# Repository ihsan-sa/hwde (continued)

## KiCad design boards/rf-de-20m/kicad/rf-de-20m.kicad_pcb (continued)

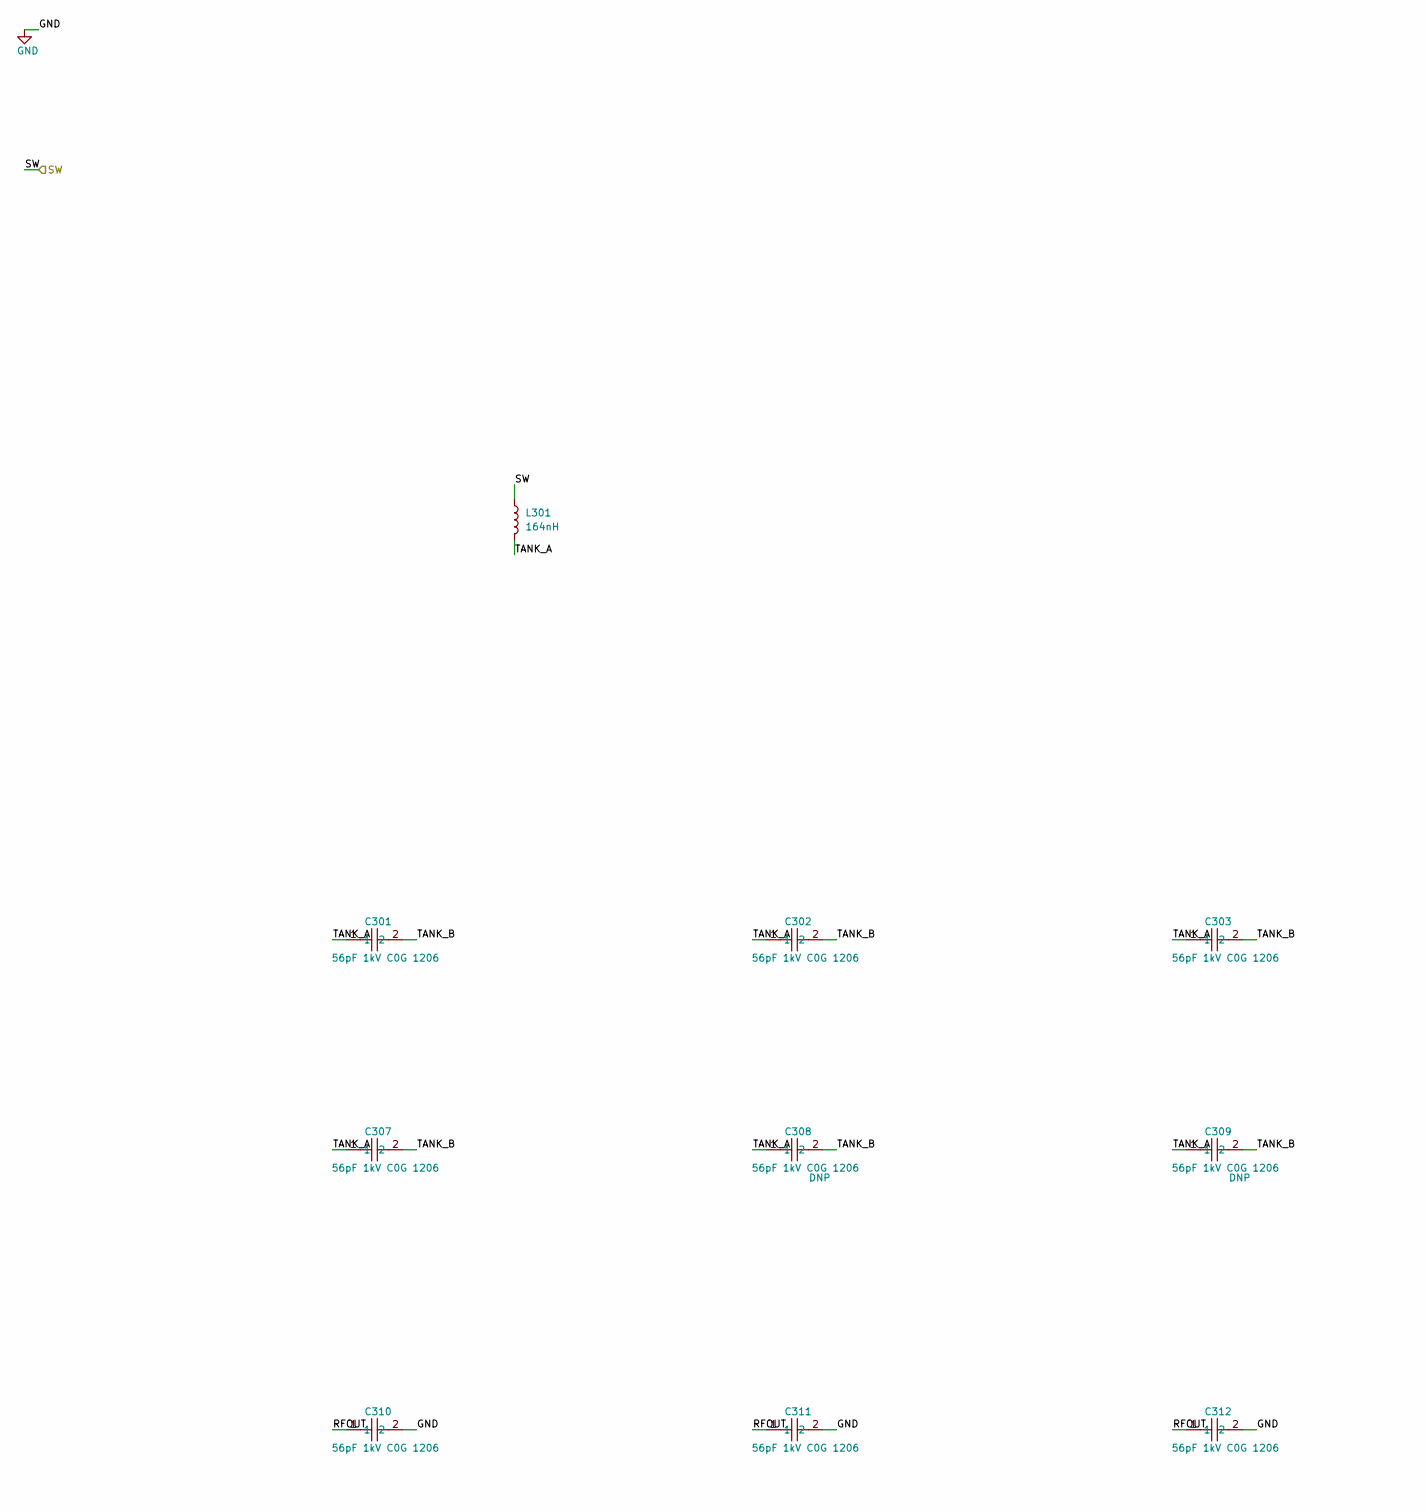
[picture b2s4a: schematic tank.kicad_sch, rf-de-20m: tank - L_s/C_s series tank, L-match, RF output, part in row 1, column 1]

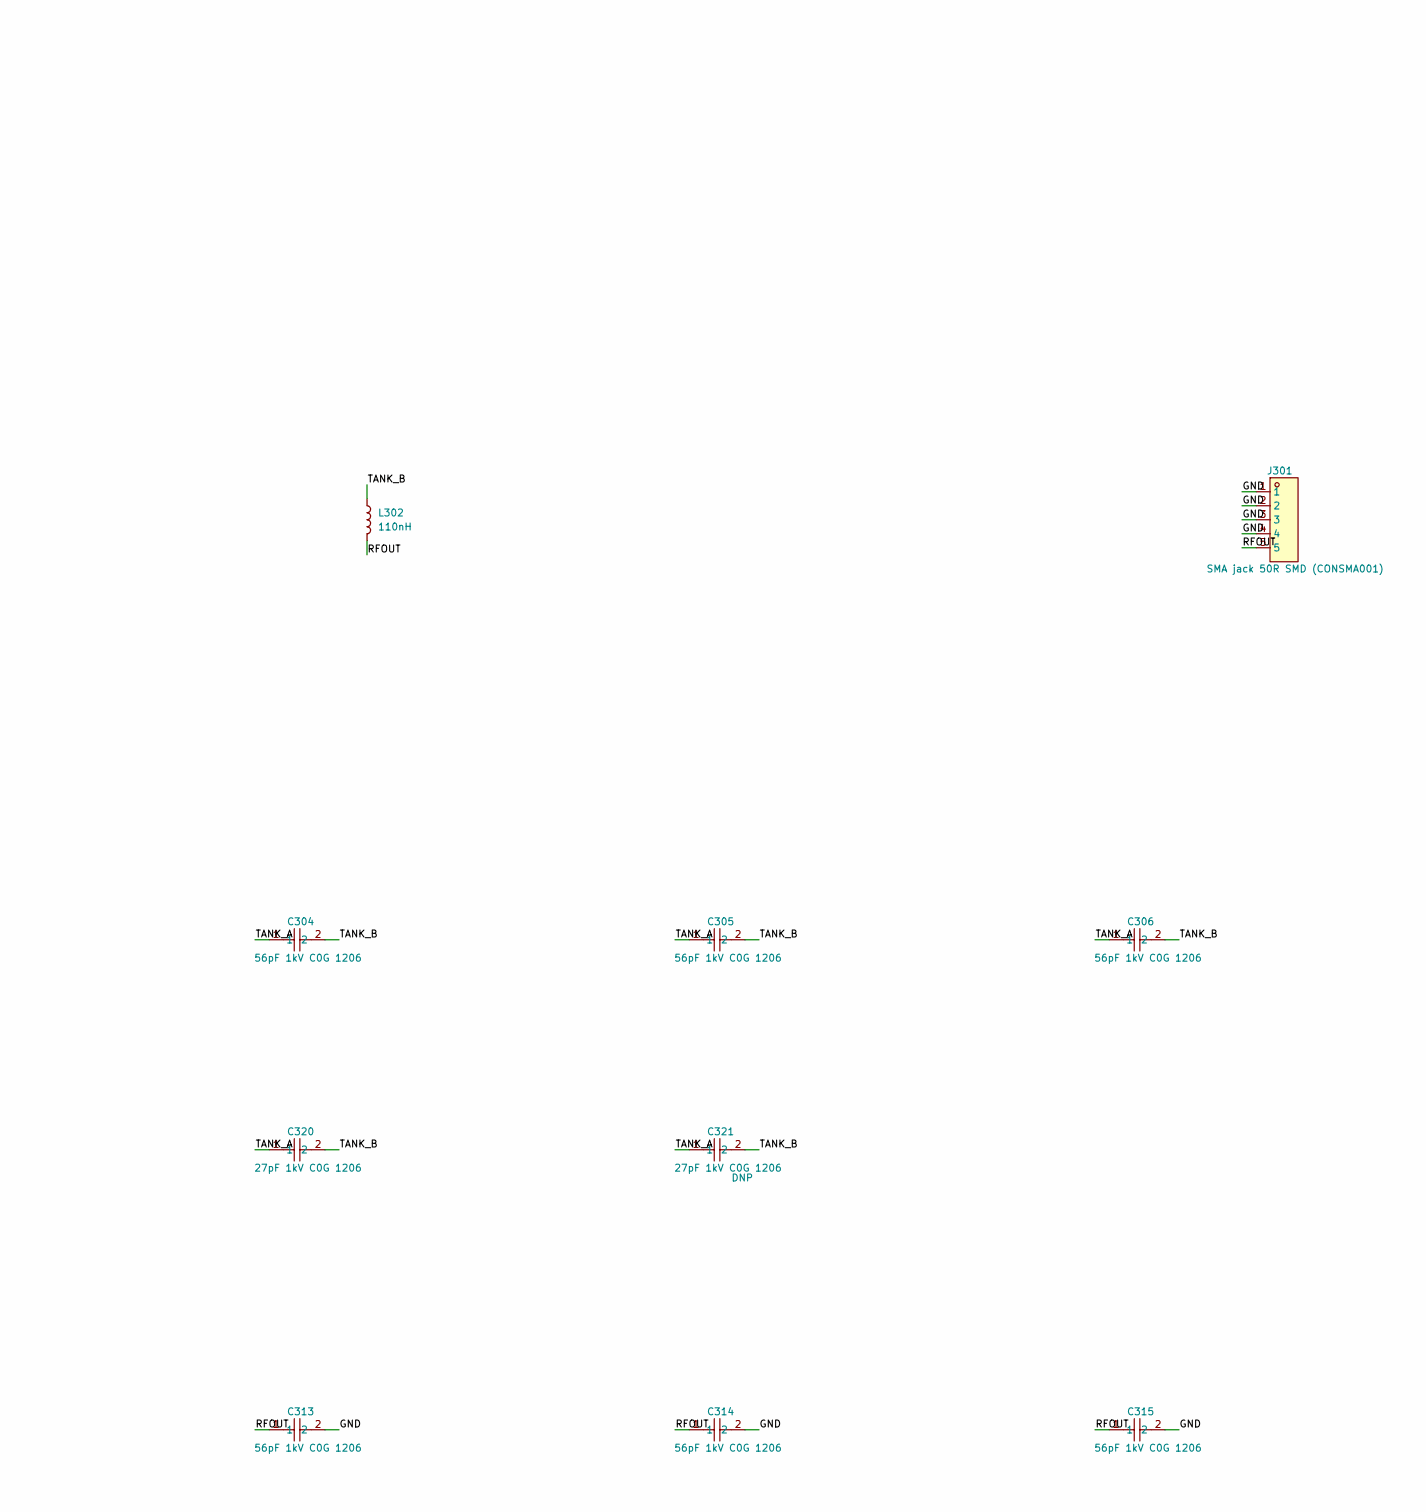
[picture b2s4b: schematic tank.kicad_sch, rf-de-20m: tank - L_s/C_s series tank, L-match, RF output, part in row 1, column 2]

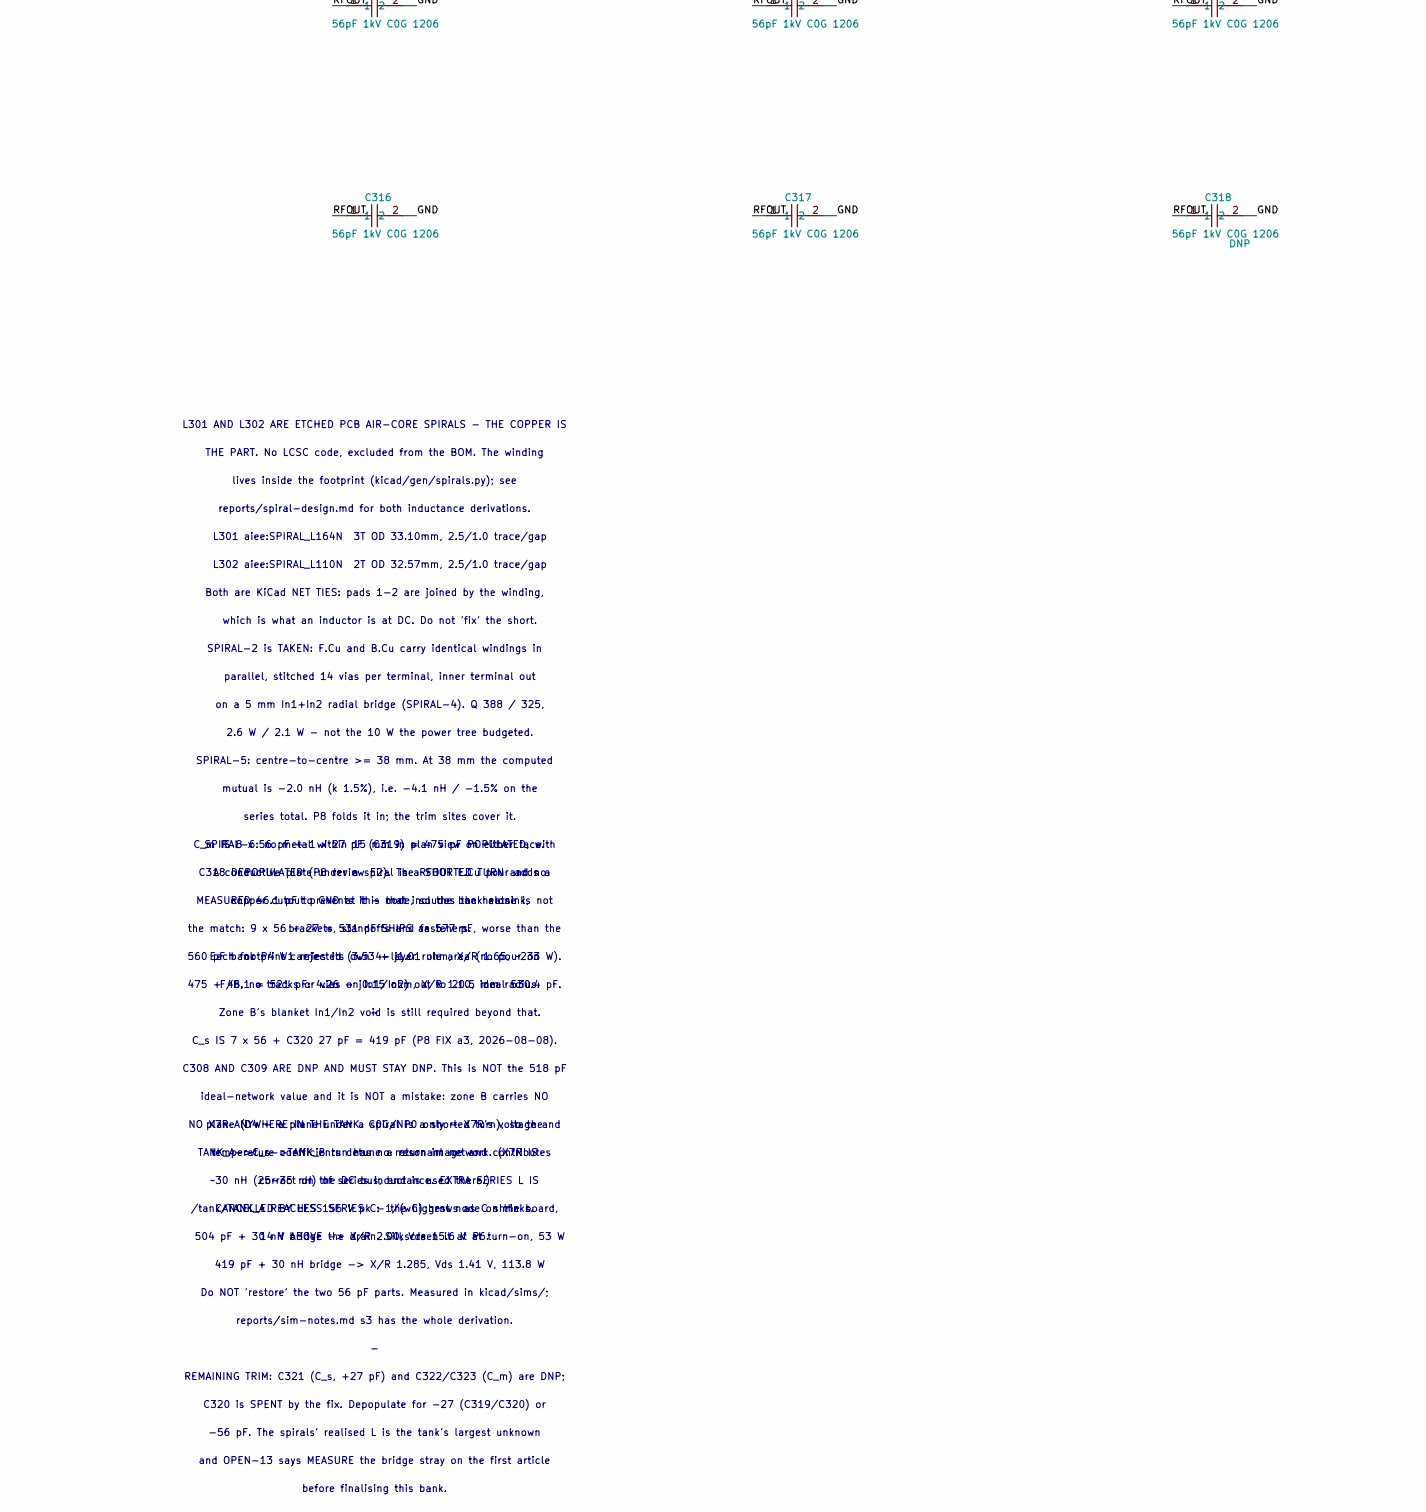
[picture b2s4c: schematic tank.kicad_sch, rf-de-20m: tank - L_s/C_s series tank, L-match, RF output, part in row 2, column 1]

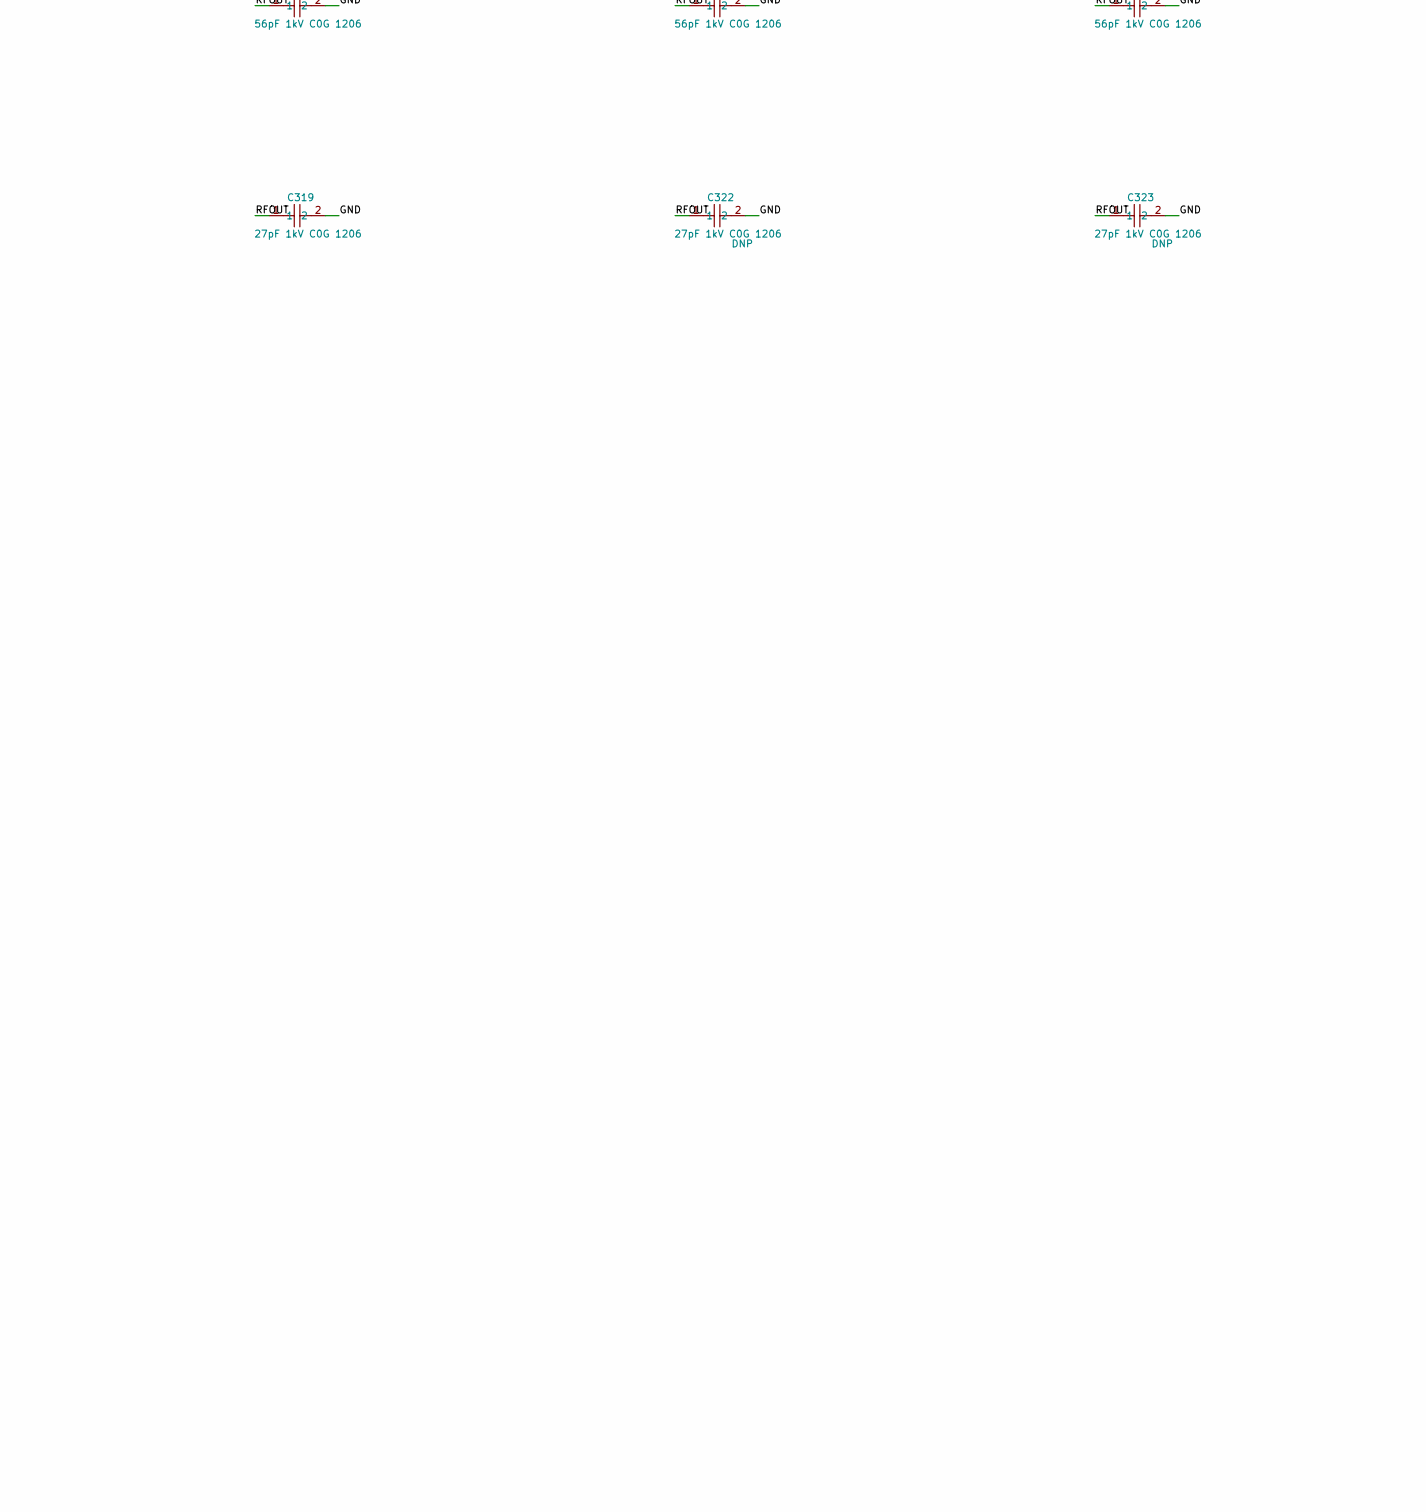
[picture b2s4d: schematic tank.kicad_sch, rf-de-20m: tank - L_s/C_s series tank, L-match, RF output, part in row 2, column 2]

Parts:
C301, C302, C303, C304, C305, C306, C307, C308, C309, C310, C311, C312, C313, C314, C315, C316, C317, C318: 56pF 1kV C0G 1206; C1206; LCSC C113875
C319, C320, C321, C322, C323: 27pF 1kV C0G 1206; C1206; LCSC C541492
J301: SMA jack 50R SMD (CONSMA001); SMA-SMD_CONSMA001-SMD-G-T; LCSC C22418168
L301: 164nH; SPIRAL_L164N
L302: 110nH; SPIRAL_L110N

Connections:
/SW: L301.1; also elsewhere on the board
/tank/RFOUT: C310.1, C311.1, C312.1, C313.1, C314.1, C315.1, C316.1, C317.1, C318.1, C319.1, C322.1, C323.1, J301.5, L302.2
/tank/TANK_A: C301.1, C302.1, C303.1, C304.1, C305.1, C306.1, C307.1, C308.1, C309.1, C320.1, C321.1, L301.2
/tank/TANK_B: C301.2, C302.2, C303.2, C304.2, C305.2, C306.2, C307.2, C308.2, C309.2, C320.2, C321.2, L302.1
GND: C310.2, C311.2, C312.2, C313.2, C314.2, C315.2, C316.2, C317.2, C318.2, C319.2, C322.2, C323.2, J301.1, J301.2, J301.3, J301.4; also elsewhere on the board

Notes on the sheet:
L301 AND L302 ARE ETCHED PCB AIR-CORE SPIRALS - THE COPPER IS
THE PART. No LCSC code, excluded from the BOM. The winding
lives inside the footprint (kicad/gen/spirals.py); see
reports/spiral-design.md for both inductance derivations.
L301 aiee:SPIRAL_L164N 3T OD 33.10mm, 2.5/1.0 trace/gap
L302 aiee:SPIRAL_L110N 2T OD 32.57mm, 2.5/1.0 trace/gap
Both are KiCad NET TIES: pads 1-2 are joined by the winding,
which is what an inductor is at DC. Do not 'fix' the short.
SPIRAL-2 is TAKEN: F.Cu and B.Cu carry identical windings in
parallel, stitched 14 vias per terminal, inner terminal out
on a 5 mm In1+In2 radial bridge (SPIRAL-4). Q 388 / 325,
2.6 W / 2.1 W - not the 10 W the power tree budgeted.
SPIRAL-5: centre-to-centre >= 38 mm. At 38 mm the computed
mutual is -2.0 nH (k 1.5%), i.e. -4.1 nH / -1.5% on the
series total. P8 folds it in; the trim sites cover it.
SPIRAL-6: no metal within 15 mm in plan view on either face.
A conductive plate under a spiral is a SHORTED TURN and no
copper cutout prevents it - that includes the heatsink,
brackets, standoffs and fasteners.
Each footprint carries its own 4-layer rule area (no pour on
F/B, no tracks or vias on In1/In2) out to 20.5 mm radius.
Zone B's blanket In1/In2 void is still required beyond that.
C_m IS 8 x 56 pF + 1 x 27 pF (C319) = 475 pF POPULATED, with
C318 DEPOPULATED (P8 review E2). The RFOUT F.Cu pour adds a
MEASURED 46.1 pF to GND at this node, so the bank alone is not
the match: 9 x 56 + 27 = 531 pF SHIPS as 577 pF, worse than the
560 pF bank P4 W1 rejected (3.53 + j1.01 ohm, X/R 1.65, ~233 W).
475 + 46.1 = 521 pF: 4.26 - j0.15 ohm, X/R 1.10, ideal 530.4 pF.
C_s IS 7 x 56 + C320 27 pF = 419 pF (P8 FIX a3, 2026-08-08).
C308 AND C309 ARE DNP AND MUST STAY DNP. This is NOT the 518 pF
ideal-network value and it is NOT a mistake: zone B carries NO
plane (D4 - a plane under a spiral is a shorted turn), so the
TANK_A->C_s->TANK_B run has no return image and contributes
~30 nH (25-35 nH) of series inductance. EXTRA SERIES L IS
CANCELLED BY LESS SERIES C: 1/(wC) grows as C shrinks.
504 pF + 30 nH bridge -> X/R 2.00, Vds 15.6 V at turn-on, 53 W
419 pF + 30 nH bridge -> X/R 1.285, Vds 1.41 V, 113.8 W
Do NOT 'restore' the two 56 pF parts. Measured in kicad/sims/;
reports/sim-notes.md s3 has the whole derivation.
REMAINING TRIM: C321 (C_s, +27 pF) and C322/C323 (C_m) are DNP;

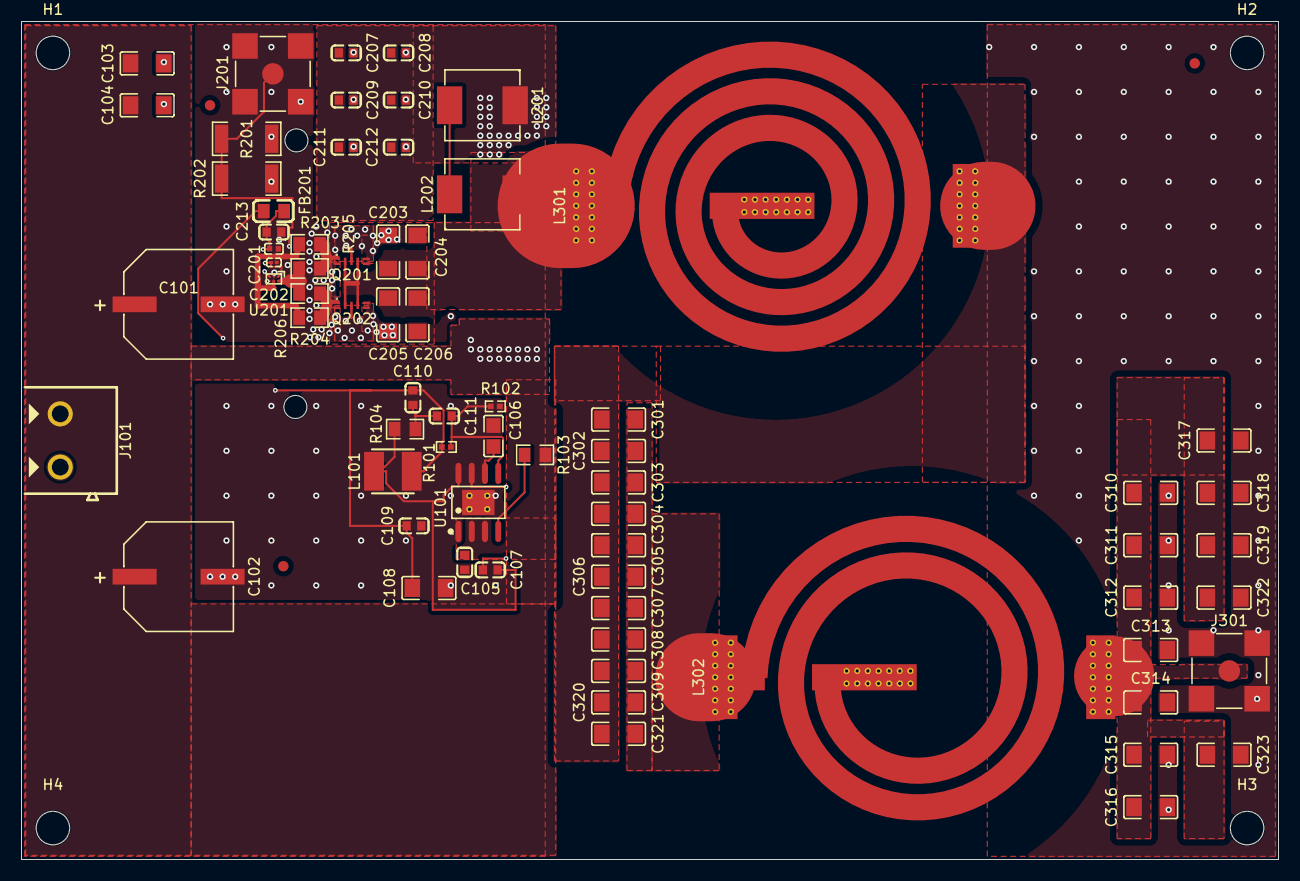
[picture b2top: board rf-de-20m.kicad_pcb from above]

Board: 4 copper layers, 120.0 x 80.0 mm, 80 parts (0 on the bottom side), 20 nets.

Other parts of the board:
FID1, FID2, FID3: Fiducial_1mm_Mask2mm
H1, H2, H3, H4: MountingHole_3.2mm_M3
H5, H6: MountingHole_2.2mm_M2_ISO7380
HS1: HEATSINK_LAND; HS2_HEATSINK_LAND

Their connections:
GND: HS1.1; also elsewhere on the board

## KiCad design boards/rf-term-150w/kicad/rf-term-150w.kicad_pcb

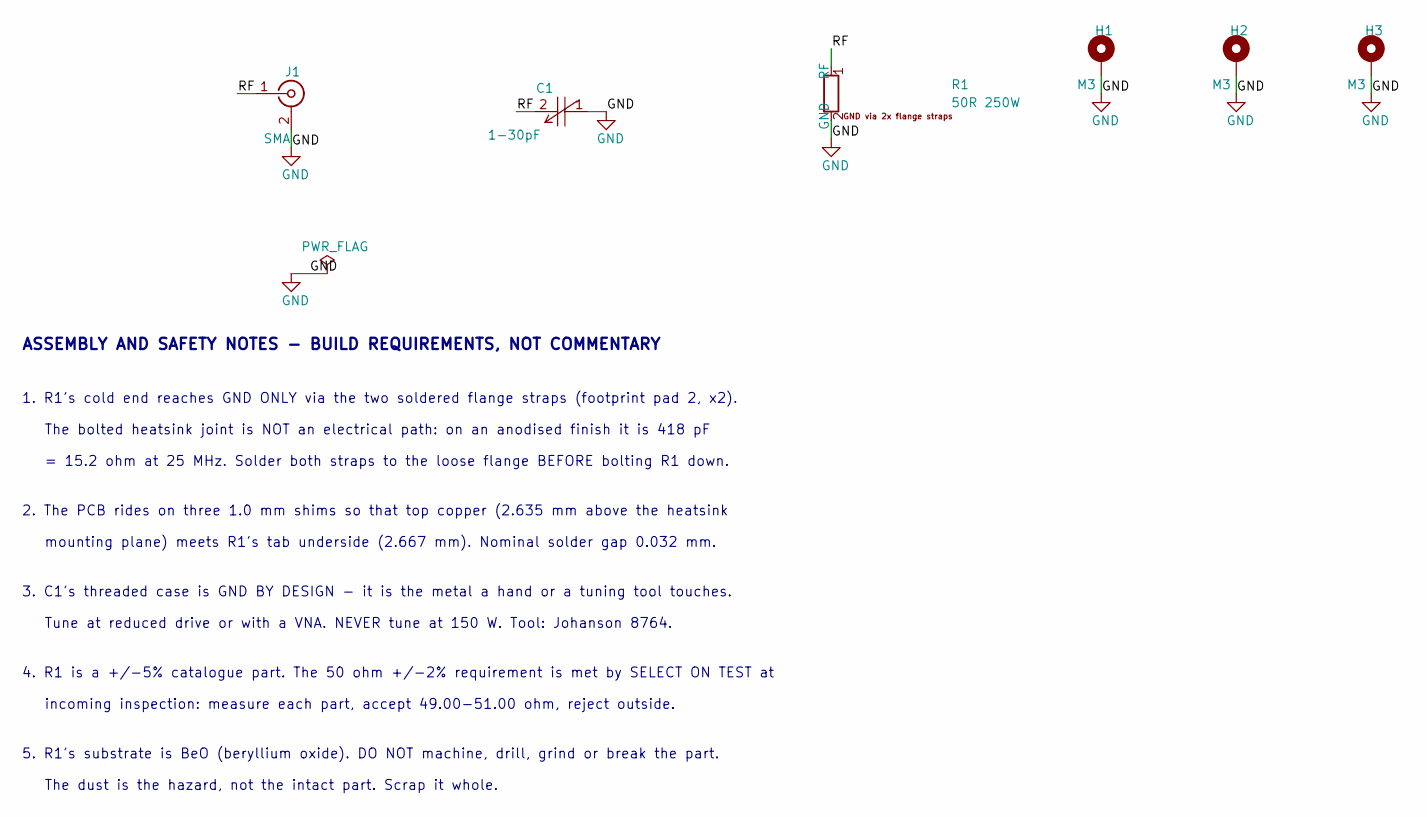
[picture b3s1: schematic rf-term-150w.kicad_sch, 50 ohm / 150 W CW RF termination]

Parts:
C1: 1-30pF; CAP-ADJ-TH_2P-BD7.5_5602; MPN 5602; DigiKey 1956-1000-ND
H1, H2, H3: M3; MountingHole_3.2mm_M3_Pad_5.0mm
J1: SMA; SMA_BAT_Wireless_BWSMA-KWE-Z001; MPN SMA-KWE; LCSC C7498154
R1: 50R 250W; R_LapPad_T50R0-250-12X; MPN T50R0-250-12X; DigiKey 4353-T50R0-250-12X-ND

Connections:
/RF: C1.2 (ROTOR), J1.1 (In), R1.1 (RF)
GND: C1.1 (STATOR), H1.1, H2.1, H3.1, J1.2 (Ext), R1.2 (GND)

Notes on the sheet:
ASSEMBLY AND SAFETY NOTES - BUILD REQUIREMENTS, NOT COMMENTARY
1. R1's cold end reaches GND ONLY via the two soldered flange straps (footprint pad 2, x2).
The bolted heatsink joint is NOT an electrical path: on an anodised finish it is 418 pF
= 15.2 ohm at 25 MHz. Solder both straps to the loose flange BEFORE bolting R1 down.
2. The PCB rides on three 1.0 mm shims so that top copper (2.635 mm above the heatsink
mounting plane) meets R1's tab underside (2.667 mm). Nominal solder gap 0.032 mm.
3. C1's threaded case is GND BY DESIGN - it is the metal a hand or a tuning tool touches.
Tune at reduced drive or with a VNA. NEVER tune at 150 W. Tool: Johanson 8764.
4. R1 is a +/-5% catalogue part. The 50 ohm +/-2% requirement is met by SELECT ON TEST at
incoming inspection: measure each part, accept 49.00-51.00 ohm, reject outside.
5. R1's substrate is BeO (beryllium oxide). DO NOT machine, drill, grind or break the part.
The dust is the hazard, not the intact part. Scrap it whole.

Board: 2 copper layers, 6 parts (0 on the bottom side), 2 nets, no tracks yet.

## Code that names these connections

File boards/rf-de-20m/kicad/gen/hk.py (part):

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TWO OTHER P3 PLACEHOLDERS RESOLVED HERE (parts.json asked P4 to size them)
--------------------------------------------------------------------------
  * **R103 (RON) = 100 k stands, but the PACKAGE moved 0402 -> 0805.**
    (P4 review W2.) RON sits from the RON pin - held near ground by the
    on-timer - to +40V, so the FULL bus stands across one chip resistor
    continuously. A thick-film 0402's maximum WORKING voltage is 50 V, so
    40 V DC is 80 % of it with nothing left for the ~51 V LC turn-on
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  re-VALUEs it to "+40V" - a power symbol's exported net name is its VALUE
  field (LEARNINGS 2026-07-28 [kicad]).
* Six nets are sheet-internal and come out `/hk/<NAME>`: VCC, BST, BUCK_SW,
  FB, RON, RINJ. No constraint references any of them.
* **The buck's switch node is called BUCK_SW, not SW.** `/SW` is the RF drain
  node on `stage`/`tank` and is named in six constraints.json entries; a
  second net called SW anywhere would be a different net with a colliding
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    # L101 - buck inductor, BUCK_SW -> +5V. 22 uH: see docstring.
    _add(sh, "L101", S_L101, V_L101, (152.4, 279.4), footprint=F_L101,
         expect={"1": "1", "2": "2"})
    sh.wire_pins("L101", {"1": BUCK_SW, "2": V5})

    # C107 - BOOTSTRAP, BST to SW. 10 nF per datasheet s8.2.1.2.6 (P3's
    # 2.2 nF was explicitly a placeholder). Must withstand BST-to-SW abs max
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    _add(sh, "C107", S_C10N_100V, V_C10N, (228.6, 279.4), footprint=F_C0603,
         expect={"1": "1", "2": "2"},
         note="Bootstrap BST-SW, 0.01uF per LM5017 s8.2.1.2.6")
    sh.wire_pins("C107", {"1": BST, "2": BUCK_SW})

    # Output bulk + HF on +5V. C108 is the COUT the ripple-injection network
    # exists to compensate for (its ESR is far below the 25 mV COT floor).
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    sh.wire_pins("R102", {"1": FB, "2": GND})

    # RON sets the on-time and therefore fSW. The datasheet puts this resistor
    # from the RON pin TO VIN (s5 pin table) - not to ground - because the
    # on-time is programmed as a function of VIN. 0805, NOT 0402: the whole
    # bus stands across it continuously and an 0402 tops out at 50 V (W2).
    _add(sh, "R103", S_R100K, V_R100K, (215.9, 355.6), footprint=F_R0805,
         expect={"1": "1", "2": "2"},
         note="RON to VIN - fSW = VOUT/(K.RON) = 562 kHz. 0805/150V: 40V "
              "continuous, ~51V on the turn-on ring")
    sh.wire_pins("R103", {"1": RON, "2": V40})

    # ---------------- Type 3 ripple injection (datasheet Table 1) ----------
    # SW --Rr-- RINJ --Cr-- VOUT, and RINJ --Cac-- FB. Cr returns to the
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         expect={"1": "1", "2": "2"},
         note="Rr - Type 3 ripple injection (LM5017 s7.3.11). 0805/150V: it "
              "stands off VIN-VOUT = 35V, ~46V on the turn-on ring")
    sh.wire_pins("R104", {"1": BUCK_SW, "2": RINJ})
    _add(sh, "C110", S_C1N_100V, V_C1N, (342.9, 355.6), footprint=F_C0603,
         expect={"1": "1", "2": "2"}, note="Cr - ramp integrator, returns to VOUT")
    sh.wire_pins("C110", {"1": RINJ, "2": V5})
    _add(sh, "C111", S_C100N_100V, V_C100N, (406.4, 355.6), footprint=F_C0603,
         expect={"1": "1", "2": "2"}, note="Cac - ac couples the ramp into FB")
    sh.wire_pins("C111", {"1": RINJ, "2": FB})

    # =====================================================================
    # sheet notes
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
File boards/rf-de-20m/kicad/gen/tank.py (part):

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* `SW` is the ONLY hierarchical pin. It crosses the root (also exposed by
  `stage`), so the net comes out **`/SW`**.
* Three nets are sheet-internal and come out `/tank/<NAME>`: TANK_A, TANK_B,
  RFOUT - exactly the spellings constraints.json uses.
* `+40V` and `+5V` do not appear on this sheet at all.

NOT ON THIS SHEET
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         note="L_s - ETCHED PCB AIR-CORE SPIRAL (net tie, pads 1-2 joined by "
              "the winding). 3T OD 33.1mm F.Cu||B.Cu. NO plane or heatsink "
              "beneath - shorted turn. See reports/spiral-design.md")
    sh.wire_pins("L301", {"1": SW, "2": TANK_A})

    # C_s bank: 7 x 56 pF + C320 27 pF = 419 pF POPULATED (P8 fix a3; C308,
    # C309 and C321 are DNP). NOT 504 pF and NOT the 518 pF ideal-network
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             (88.9 + (i % 6) * 76.2, 190.5 + (i // 6) * 38.1),
             footprint=F_C1206, expect={"1": "1", "2": "2"}, dnp=dnp,
             note=_cs_note(ref, pf, dnp))
        sh.wire_pins(ref, {"1": TANK_A, "2": TANK_B})

    # =====================================================================
    # B8 - L-match to 50 ohm
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         note="L_m - ETCHED PCB AIR-CORE SPIRAL (net tie, pads 1-2 joined by "
              "the winding). 2T OD 32.57mm F.Cu||B.Cu. Centre-to-centre "
              ">=38mm from L301 (SPIRAL-5). See reports/spiral-design.md")
    sh.wire_pins("L302", {"1": TANK_B, "2": RFOUT})

    # C_m bank: 8 x 56 + 1 x 27 = 475 pF POPULATED (C318 depopulated at P8,
    # review E2) + 46.1 pF of RFOUT pour = 521 pF against the 530.4 pF ideal
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                   "C_m bank 8x56+1x27 = 475pF populated; the RFOUT pour "
                   "adds 46.1pF -> 521pF against the 530.4pF ideal. Carries "
                   "6.66A rms, not the 2A load current"))
        sh.wire_pins(ref, {"1": RFOUT, "2": GND})

    # =====================================================================
    # B9 - RF output
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    _add(sh, "J301", S_SMA, V_SMA, (495.3, 114.3), footprint=F_SMA,
         expect={str(n): str(n) for n in range(1, 6)},
         note="RF out, 200 W. SILK: burn + RF-exposure hazard (sheets.md s6.8)")
    sh.wire_pins("J301", {"1": GND, "2": GND, "3": GND, "4": GND, "5": RFOUT})

    # =====================================================================
    # sheet notes
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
